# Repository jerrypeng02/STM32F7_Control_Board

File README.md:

## STM32F7_Control_Board

## Purpose:
In Sensor Systems Lab, there is a PR2 robot that has the internal cable connecting proximity sensors to the computer for trasmitting data. However, we want an application that can employ this feature on other robots. So for this application, it does not require the robot to have the internal cable. It can transfer the data from registers in proximity sensors to the Wi-Fi hub and send the data back to a computer wirelessly.

---

## Requirement:

System: Windows 7 or higher

Hardware: STM32F411E Discovery board

Software: STM32CubeMX, Keil uVision IDE with MDK-ARM toolchain, Putty

---

## Hardware construction:

The hardware has three parts: I2C to connectors, microcontroller, and the USB
I2C: the I2C circuits are for connecting the proximity sensors. (The connectors are FFC & FPC connectors)
Microcontroller: STM32F723 microcontroller, which has embedded PHY chip for the USB 2.0
USB: the USB circuits consist of suggested ESD protection (Check details from datasheet of ECMF02-2AMX6)
The rest of the components are mostly capacitors and resistors. Resistors are for LEDs and as pull-up resistors. Capacitors are as simple low pass filters for filtering high frequency noise signals for pairs of VDD and VSS on microcontroller.

---

## Configuration:

**Pre-connection:**
Disconnect the 2 jumpers from CN3 on STM32F411 Discovery board for programming/debugging external STM32 application and connect CN2 debug connector to the connector on the control board (Check details on the datasheet from STM32F411 discovery board)

**Use the STM32CubeMX to configure the following setting of the microcontroller:**

**Peripherals:**

I2C: I2C1

RCC: High Speed Clock (HSE) -> Crystal/Ceramic Resonator

SYS: Debug -> Serial Wire

USB_STG_HS: Internal Phy -> Device_Only, Active_VBUS checkbox

**MiddleWares:**

USB_DEVICE: Classs for HS IP -> Communication Device Class (Virtual Port Com)

**On_board:**

Configure PE2 as GPIO_Output

---

## Code:

The main method includes the initiation of the gpio expander device for controlling each VL6180 device in the array, turning all VL6180 devices off, turning the VL6180 devices on one by one and changing the its slave address, and finally testing if the application can send out string over the USB to the computer and shown on a terminal through virtual communication port.

---

## Testing:

Note that there are two tests for now: testing if the application can send only stirng to the terminal, and testing if the terminal can receive different string according to user input as keys.

For the first test, define the macro SEND_ONLY in main.c. For the second test, define the macro CALLBACK in main.c, usbd_cdc_if.c and usbd_cdc_if.h. In line 333 of the usbd_cdc_if.c and in line 140 of the usbd_cdc_if.h, the declaration of the weak object function for the call back function is for making the call back in the USB receive cdc function, which is in line 302 of the usbd_cdc_if.c. And the actual call back action is defined in main.c, which is in line 207.

*Detailed setting can be refered in [video](https://www.youtube.com/watch?v=7oED-m34EKk)*

---

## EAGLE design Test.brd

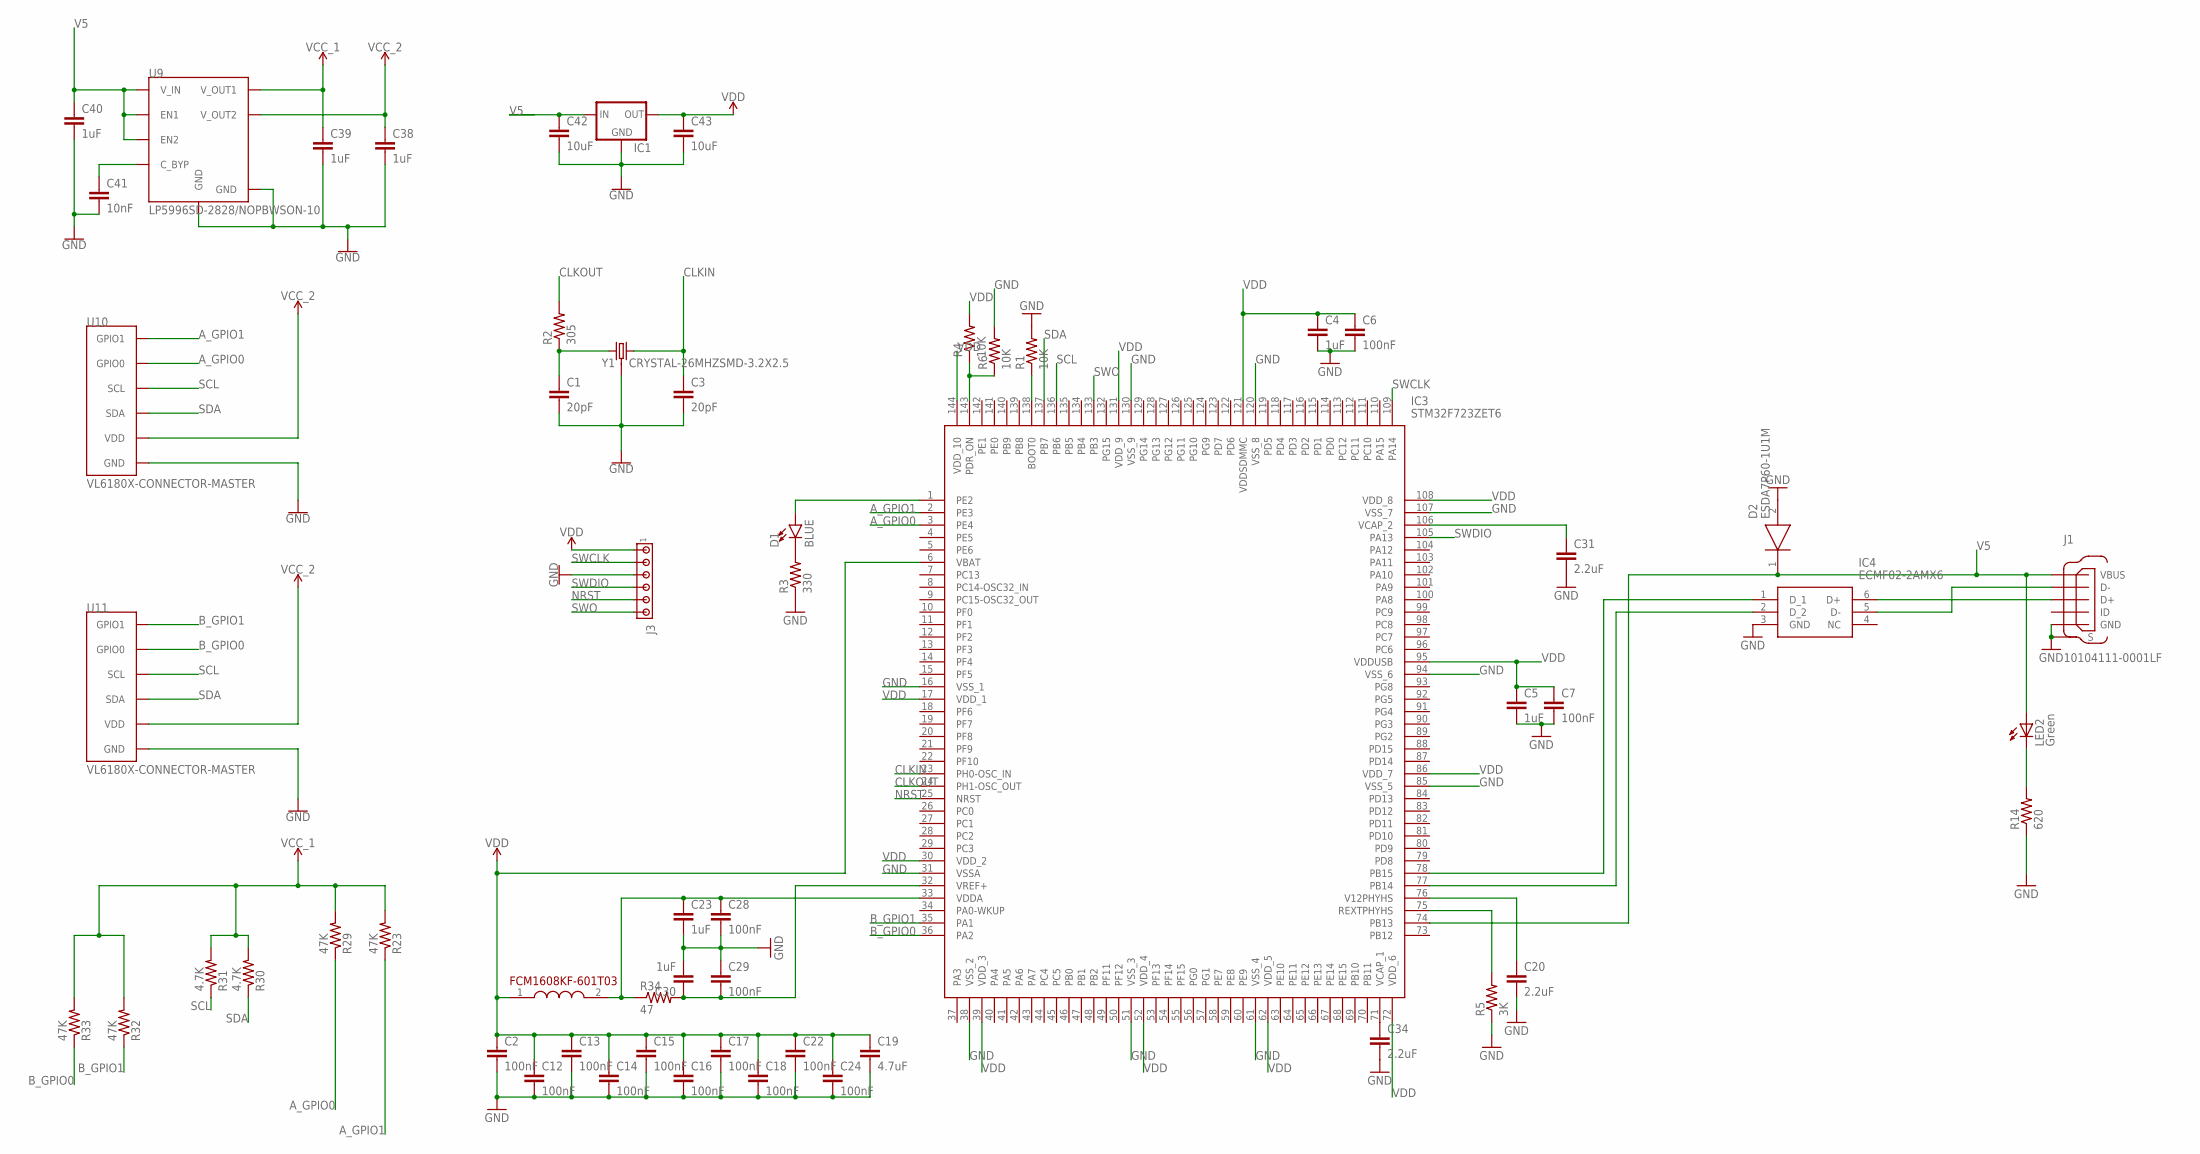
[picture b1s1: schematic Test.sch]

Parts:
C1, C3: 20pF; C0603
C2, C6, C7, C12, C13, C14, C15, C16, C17, C18, C22, C24, C28, C29: 100nF; C0603K
C4, C5, C23, C30, C38, C39, C40: 1uF; C0603K
C19: 4.7uF; C0603K
C20, C31, C34: 2.2uF; C0603K
C41: 10nF; C0603K
C42, C43: 10uF; C0603K
D1: BLUE; LED-0603
D2: ESDA7P60-1U1M; ESDA7P601U1M
FCM1608KF: FCM1608KF-601T03
IC1: LM1117; SOT223
IC3: STM32F723ZET6; QFP50P2200X2200X160-144N
IC4: ECMF02-2AMX6; SON50P150X170X55-6N
J1: 10104111-0001LF; FRAMATOME_10104111-0001LF
J3: MTA06-100; 10X06MTA
LED2: Green; CHIP-LED0603
R1, R4, R6: 10K; R0603
R2: 305; R0603
R3: 330; R0603
R5: 3K; R0603
R14: 620; R0603
R23, R29, R32, R33: 47K; R0603
R30, R31: 4.7K; R0603
R34: 47; R0603
U9: LP5996SD-2828/NOPBWSON-10; WSON-10
U10, U11: VL6180X-CONNECTOR-MASTER; FH33-6S-0.5SH(10)-MASTER
Y1: CRYSTAL-26MHZSMD-3.2X2.5; CRYSTAL-SMD-3.2X2.5MM

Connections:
A_GPIO0: IC3.3 (PE4), R29.1, U10.2 (GPIO0)
A_GPIO1: IC3.2 (PE3), R23.1, U10.1 (GPIO1)
B_GPIO0: IC3.36 (PA2), R33.1, U11.2 (GPIO0)
B_GPIO1: IC3.35 (PA1), R32.1, U11.1 (GPIO1)
CLKIN: C3.1, IC3.23 (PH0-OSC_IN), Y1.3 (2)
CLKOUT: IC3.24 (PH1-OSC_OUT), R2.2
GND: C1.2, C2.2, C3.2, C4.2, C5.2, C6.2, C7.2, C12.2, C13.2, C14.2, C15.2, C16.2, C17.2, C18.2, C19.2, C20.2, C22.2, C23.2, C24.2, C28.2, C29.1, C30.2, C31.2, C34.2, C38.2, C39.2, C40.2, C41.2, C42.2, C43.2, D2.2 (A), IC1.1 (GND), IC3.16 (VSS_1), IC3.31 (VSSA), IC3.38 (VSS_2), IC3.51 (VSS_3), IC3.61 (VSS_4), IC3.85 (VSS_5), IC3.94 (VSS_6), IC3.107 (VSS_7), IC3.120 (VSS_8), IC3.130 (VSS_9), IC4.3 (GND), J1.5 (GND), J1.6 (S), J1.7 (S), J1.8 (S), J1.9 (S), J3.3, R1.2, R3.1, R5.1, R6.2, R14.1, U9.6 (GND), U9.11 (GND), U10.6 (GND), U11.6 (GND), Y1.2 (3), Y1.4 (3)
unnamed: IC3.138 (BOOT0), R1.1
unnamed: LED2.C, R14.2
unnamed: C34.1, IC3.71 (VCAP_1)
unnamed: C20.1, IC3.76 (V12PHYHS)
unnamed: D1.C, R3.2
unnamed: C31.1, IC3.106 (VCAP_2)
unnamed: IC3.78 (PB15), IC4.1 (D_1)
unnamed: IC3.77 (PB14), IC4.2 (D_2)
unnamed: D1.A, IC3.1 (PE2)
unnamed: C23.1, C28.1, FCM1608KF.2 (2.OUT), IC3.33 (VDDA), R34.1
unnamed: IC4.6 (D+), J1.3 (D+)
unnamed: C1.1, R2.1, Y1.1
unnamed: IC4.5 (D-), J1.2 (D-)
unnamed: IC3.143 (PDR_ON), R4.1, R6.1
unnamed: IC3.75 (REXTPHYHS), R5.2
unnamed: C29.2, C30.1, IC3.32 (VREF+), R34.2
unnamed: C41.1, U9.4 (C_BYP)
NRST: IC3.25 (NRST), J3.5
SCL: IC3.136 (PB6), R31.1, U10.3 (SCL), U11.3 (SCL)
SDA: IC3.137 (PB7), R30.1, U10.4 (SDA), U11.4 (SDA)
SWCLK: IC3.109 (PA14), J3.2
SWDIO: IC3.105 (PA13), J3.4
SWO: IC3.133 (PB3), J3.6
V5: C40.1, C42.1, D2.1 (K), IC1.3 (IN), IC3.74 (PB13), J1.1 (VBUS), LED2.A, U9.1 (V_IN), U9.2 (EN1), U9.3 (EN2)
VCC_1: C39.1, R23.2, R29.2, R30.2, R31.2, R32.2, R33.2, U9.10 (V_OUT1)
VCC_2: C38.1, U9.9 (V_OUT2), U10.5 (VDD), U11.5 (VDD)
VDD: C2.1, C4.1, C5.1, C6.1, C7.1, C12.1, C13.1, C14.1, C15.1, C16.1, C17.1, C18.1, C19.1, C22.1, C24.1, C43.1, FCM1608KF.1 (1.IN), IC1.2 (OUT), IC3.6 (VBAT), IC3.17 (VDD_1), IC3.30 (VDD_2), IC3.39 (VDD_3), IC3.52 (VDD_4), IC3.62 (VDD_5), IC3.72 (VDD_6), IC3.86 (VDD_7), IC3.95 (VDDUSB), IC3.108 (VDD_8), IC3.121 (VDDSDMMC), IC3.131 (VDD_9), IC3.144 (VDD_10), J3.1, R4.2

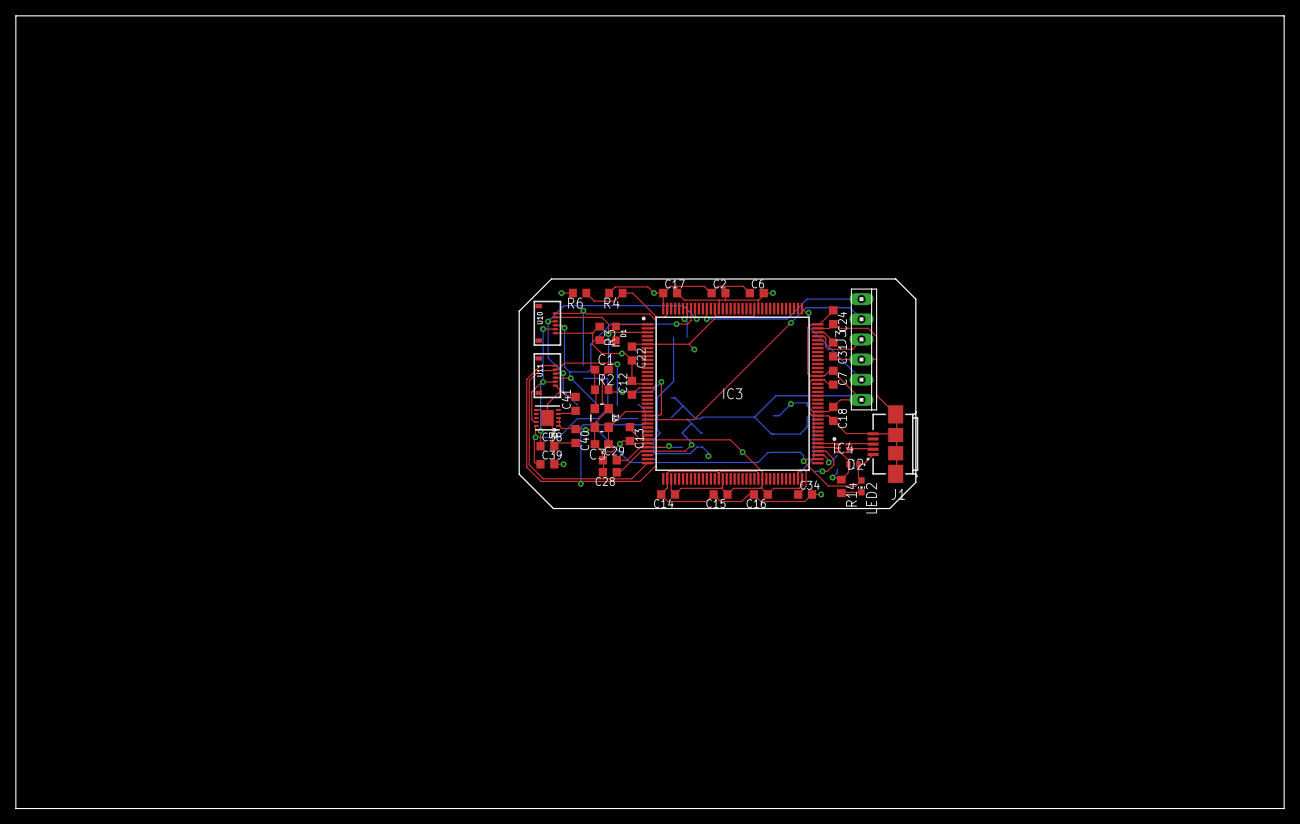
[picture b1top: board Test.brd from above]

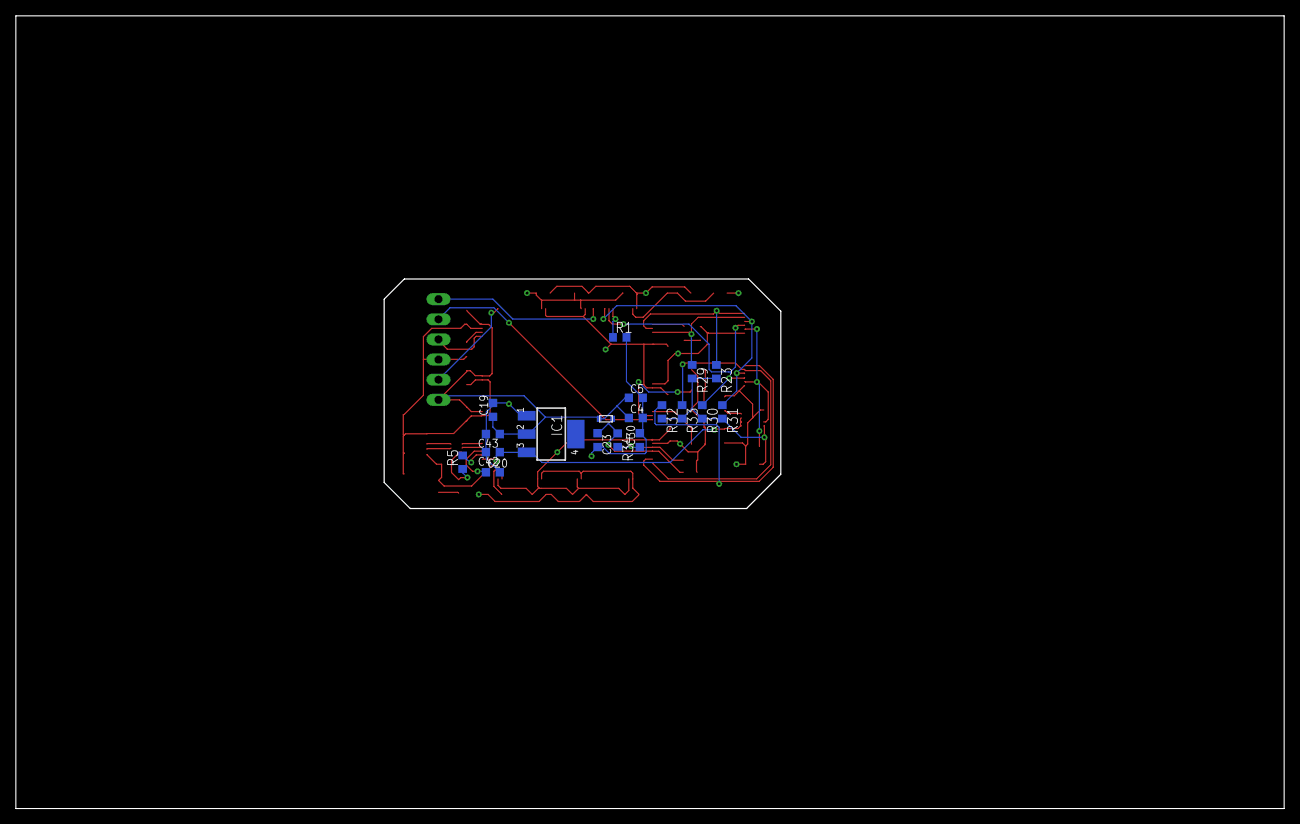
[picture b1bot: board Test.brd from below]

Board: 4 copper layers, 159.8 x 99.8 mm, 57 parts (19 on the bottom side), 34 nets.

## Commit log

2019-09-13 Edited with Bitbucket
2019-09-13 README.md edited purpose and software requirement
2019-09-13 README.md edited format
2019-09-13 README.md edited more format
2019-09-16 README.md add configuration
2019-09-16 README.md edited configuration
2019-09-19 README.md edited Code and testing
2019-09-19 README.md deleted format
2019-09-19 README.md deleted more format

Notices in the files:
parts and their libraries:
SparkFun-Clocks: Licensing: Creative Commons ShareAlike 4.0 International - https://creativecommons.org/licenses/by-sa/4.0
